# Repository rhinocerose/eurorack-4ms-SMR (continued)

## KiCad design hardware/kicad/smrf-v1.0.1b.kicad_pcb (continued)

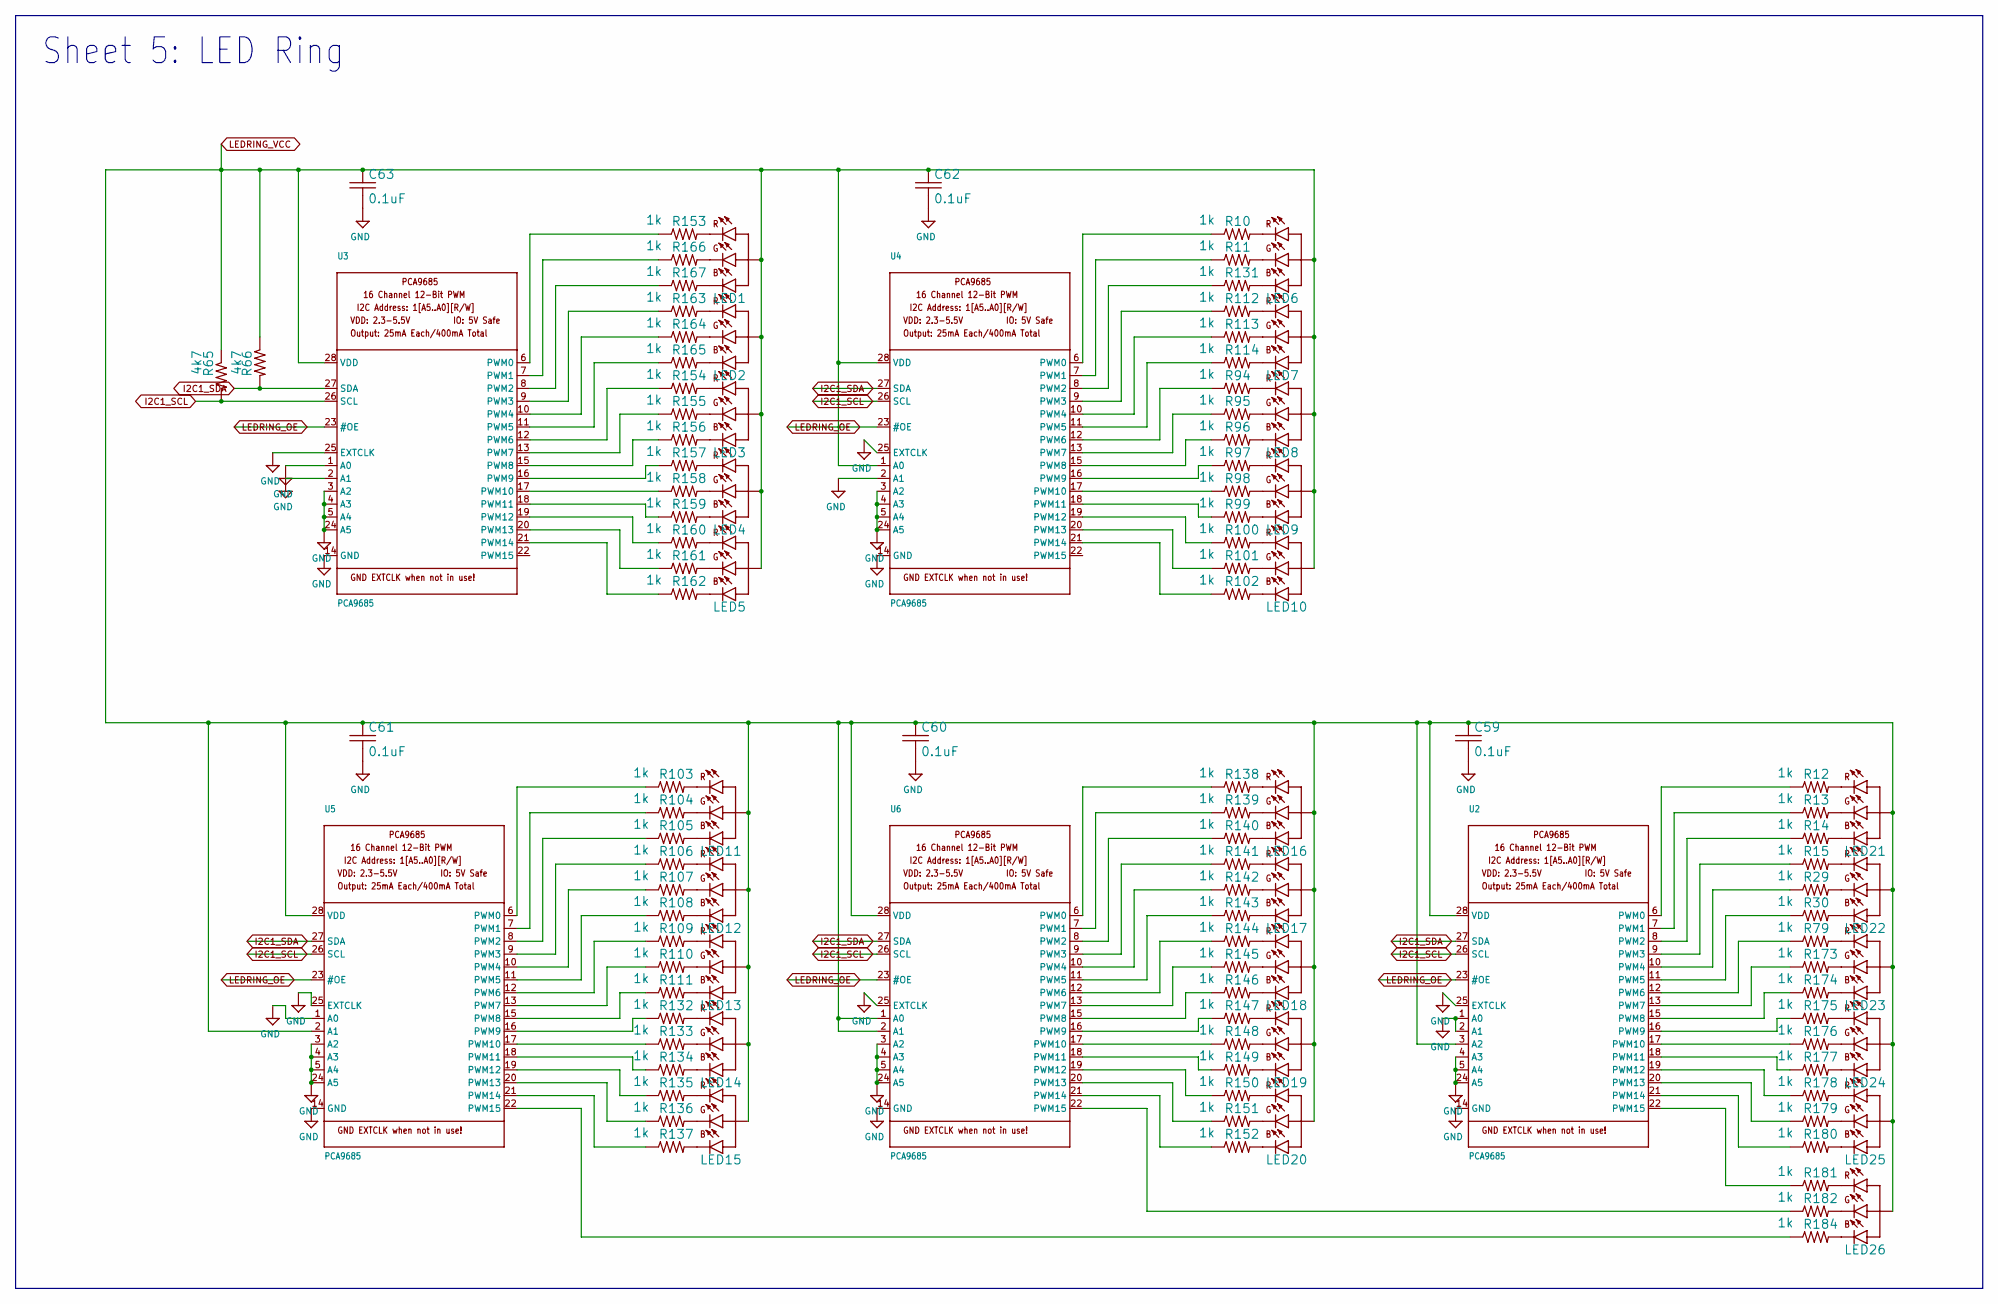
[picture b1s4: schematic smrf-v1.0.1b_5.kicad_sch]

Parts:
C59, C60, C61, C62, C63: 0.1uF; C0603
LED1, LED2, LED3, LED4, LED5, LED6, LED7, LED8, LED9, LED10, LED11, LED12, LED13, LED14, LED15, LED16, LED17, LED18, LED19, LED20, LED21, LED22, LED23, LED24, LED25, LED26: LED-RGB-CA-HEBEI; PLCC4
R10, R11, R12, R13, R14, R15, R29, R30, R79, R94, R95, R96, R97, R98, R99, R100, R101, R102, R103, R104, R105, R106, R107, R108, R109, R110, R111, R112, R113, R114, R131, R132, R133, R134, R135, R136, R137, R138, R139, R140, R141, R142, R143, R144, R145, R146, R147, R148, R149, R150, R151, R152, R153, R154, R155, R156, R157, R158, R159, R160, R161, R162, R163, R164, R165, R166, R167, R173, R174, R175, R176, R177, R178, R179, R180, R181, R182, R184: 1k; R0603
R65, R66: 4k7; R0603
U2, U3, U4, U5, U6: PCA9685; TSSOP28

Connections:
GND: C59.2, C60.2, C61.2, C62.2, C63.2, U2.1 (A0), U2.2 (A1), U2.4 (A3), U2.5 (A4), U2.14 (GND), U2.24 (A5), U2.25 (EXTCLK), U3.1 (A0), U3.2 (A1), U3.3 (A2), U3.4 (A3), U3.5 (A4), U3.14 (GND), U3.24 (A5), U3.25 (EXTCLK), U4.2 (A1), U4.3 (A2), U4.4 (A3), U4.5 (A4), U4.14 (GND), U4.24 (A5), U4.25 (EXTCLK), U5.1 (A0), U5.3 (A2), U5.4 (A3), U5.5 (A4), U5.14 (GND), U5.24 (A5), U5.25 (EXTCLK), U6.3 (A2), U6.4 (A3), U6.5 (A4), U6.14 (GND), U6.24 (A5), U6.25 (EXTCLK); also elsewhere on the board
I2C1_SCL: R65.2, U2.26 (SCL), U3.26 (SCL), U4.26 (SCL), U5.26 (SCL), U6.26 (SCL); also elsewhere on the board
I2C1_SDA: R66.2, U2.27 (SDA), U3.27 (SDA), U4.27 (SDA), U5.27 (SDA), U6.27 (SDA); also elsewhere on the board
LEDRING_OE: U2.23 (#OE), U3.23 (#OE), U4.23 (#OE), U5.23 (#OE), U6.23 (#OE); also elsewhere on the board
LEDRING_VCC: C59.1, C60.1, C61.1, C62.1, C63.1, LED1.P$2 (A), LED2.P$2 (A), LED3.P$2 (A), LED4.P$2 (A), LED5.P$2 (A), LED6.P$2 (A), LED7.P$2 (A), LED8.P$2 (A), LED9.P$2 (A), LED10.P$2 (A), LED11.P$2 (A), LED12.P$2 (A), LED13.P$2 (A), LED14.P$2 (A), LED15.P$2 (A), LED16.P$2 (A), LED17.P$2 (A), LED18.P$2 (A), LED19.P$2 (A), LED20.P$2 (A), LED21.P$2 (A), LED22.P$2 (A), LED23.P$2 (A), LED24.P$2 (A), LED25.P$2 (A), LED26.P$2 (A), R65.1, R66.1, U2.3 (A2), U2.28 (VDD), U3.28 (VDD), U4.1 (A0), U4.28 (VDD), U5.2 (A1), U5.28 (VDD), U6.1 (A0), U6.2 (A1), U6.28 (VDD); also elsewhere on the board
unnamed: LED1.P$1 (CR), R153.2
unnamed: LED1.P$4 (CG), R166.2
unnamed: R12.1, U2.6 (PWM0)
unnamed: R13.1, U2.7 (PWM1)
unnamed: R14.1, U2.8 (PWM2)
unnamed: R15.1, U2.9 (PWM3)
unnamed: LED1.P$3 (CB), R167.2
unnamed: R29.1, U2.10 (PWM4)
unnamed: R30.1, U2.11 (PWM5)
unnamed: LED2.P$1 (CR), R163.2
unnamed: LED2.P$4 (CG), R164.2
unnamed: LED2.P$3 (CB), R165.2
unnamed: LED3.P$1 (CR), R154.2
unnamed: LED3.P$4 (CG), R155.2
unnamed: LED3.P$3 (CB), R156.2
unnamed: LED4.P$1 (CR), R157.2
unnamed: LED4.P$4 (CG), R158.2
unnamed: LED4.P$3 (CB), R159.2
unnamed: R79.1, U2.12 (PWM6)
unnamed: R173.1, U2.13 (PWM7)
unnamed: R174.1, U2.15 (PWM8)
unnamed: LED5.P$1 (CR), R160.2
unnamed: LED5.P$4 (CG), R161.2
unnamed: LED5.P$3 (CB), R162.2
unnamed: LED6.P$1 (CR), R10.2
unnamed: LED6.P$4 (CG), R11.2
unnamed: LED6.P$3 (CB), R131.2
unnamed: LED7.P$1 (CR), R112.2
unnamed: LED7.P$4 (CG), R113.2
unnamed: LED7.P$3 (CB), R114.2
unnamed: LED8.P$1 (CR), R94.2
unnamed: LED8.P$4 (CG), R95.2
unnamed: LED8.P$3 (CB), R96.2
unnamed: LED9.P$1 (CR), R97.2
unnamed: LED9.P$4 (CG), R98.2
unnamed: LED9.P$3 (CB), R99.2
unnamed: LED10.P$1 (CR), R100.2
unnamed: LED10.P$4 (CG), R101.2
unnamed: LED10.P$3 (CB), R102.2
unnamed: LED11.P$1 (CR), R103.2
unnamed: R175.1, U2.16 (PWM9)
unnamed: LED11.P$4 (CG), R104.2
unnamed: LED11.P$3 (CB), R105.2
unnamed: LED12.P$1 (CR), R106.2
unnamed: LED12.P$4 (CG), R107.2
unnamed: LED12.P$3 (CB), R108.2
unnamed: LED13.P$1 (CR), R109.2
unnamed: LED13.P$4 (CG), R110.2
unnamed: LED14.P$1 (CR), R132.2
unnamed: LED14.P$4 (CG), R133.2
unnamed: LED14.P$3 (CB), R134.2
unnamed: LED15.P$1 (CR), R135.2
unnamed: LED15.P$4 (CG), R136.2
unnamed: R176.1, U2.17 (PWM10)
unnamed: R177.1, U2.18 (PWM11)
unnamed: LED15.P$3 (CB), R137.2
unnamed: LED16.P$1 (CR), R138.2
unnamed: LED16.P$4 (CG), R139.2
unnamed: LED16.P$3 (CB), R140.2
unnamed: LED17.P$1 (CR), R141.2
unnamed: LED17.P$4 (CG), R142.2
unnamed: LED17.P$3 (CB), R143.2
unnamed: LED18.P$1 (CR), R144.2
unnamed: LED18.P$4 (CG), R145.2
unnamed: LED18.P$3 (CB), R146.2
unnamed: LED19.P$1 (CR), R147.2
unnamed: LED19.P$4 (CG), R148.2
unnamed: LED19.P$3 (CB), R149.2
unnamed: LED20.P$1 (CR), R150.2
unnamed: LED20.P$4 (CG), R151.2
unnamed: LED20.P$3 (CB), R152.2
unnamed: LED13.P$3 (CB), R111.2
unnamed: R153.1, U3.6 (PWM0)
unnamed: R166.1, U3.7 (PWM1)
unnamed: R167.1, U3.8 (PWM2)
unnamed: R163.1, U3.9 (PWM3)
unnamed: R164.1, U3.10 (PWM4)
unnamed: R165.1, U3.11 (PWM5)
unnamed: R154.1, U3.12 (PWM6)
unnamed: R155.1, U3.13 (PWM7)
unnamed: R156.1, U3.15 (PWM8)
unnamed: R157.1, U3.16 (PWM9)
unnamed: R158.1, U3.17 (PWM10)
unnamed: R159.1, U3.18 (PWM11)
unnamed: R160.1, U3.19 (PWM12)
unnamed: R161.1, U3.20 (PWM13)
unnamed: R162.1, U3.21 (PWM14)
unnamed: R178.1, U2.19 (PWM12)
unnamed: R10.1, U4.6 (PWM0)
unnamed: R11.1, U4.7 (PWM1)
unnamed: R131.1, U4.8 (PWM2)
unnamed: R112.1, U4.9 (PWM3)
unnamed: R113.1, U4.10 (PWM4)
unnamed: R114.1, U4.11 (PWM5)
unnamed: R94.1, U4.12 (PWM6)
unnamed: R95.1, U4.13 (PWM7)
unnamed: R96.1, U4.15 (PWM8)
unnamed: R97.1, U4.16 (PWM9)
unnamed: R98.1, U4.17 (PWM10)
unnamed: R99.1, U4.18 (PWM11)
unnamed: R100.1, U4.19 (PWM12)
unnamed: R101.1, U4.20 (PWM13)
unnamed: R102.1, U4.21 (PWM14)
unnamed: R179.1, U2.20 (PWM13)
unnamed: R103.1, U5.6 (PWM0)
unnamed: R104.1, U5.7 (PWM1)
unnamed: R105.1, U5.8 (PWM2)
unnamed: R106.1, U5.9 (PWM3)
unnamed: R107.1, U5.10 (PWM4)
unnamed: R108.1, U5.11 (PWM5)
unnamed: R109.1, U5.12 (PWM6)
unnamed: R110.1, U5.13 (PWM7)
unnamed: R111.1, U5.15 (PWM8)
unnamed: R132.1, U5.16 (PWM9)
unnamed: R133.1, U5.17 (PWM10)
unnamed: R134.1, U5.18 (PWM11)
unnamed: R135.1, U5.19 (PWM12)
unnamed: R136.1, U5.20 (PWM13)
unnamed: R137.1, U5.21 (PWM14)
unnamed: R180.1, U2.21 (PWM14)
unnamed: LED21.P$1 (CR), R12.2
unnamed: LED21.P$4 (CG), R13.2
unnamed: LED21.P$3 (CB), R14.2
unnamed: LED22.P$1 (CR), R15.2
unnamed: LED22.P$4 (CG), R29.2
unnamed: LED22.P$3 (CB), R30.2
unnamed: LED23.P$1 (CR), R79.2
unnamed: LED23.P$4 (CG), R173.2
unnamed: LED23.P$3 (CB), R174.2
unnamed: LED24.P$1 (CR), R175.2
unnamed: LED24.P$4 (CG), R176.2
unnamed: LED24.P$3 (CB), R177.2
unnamed: R138.1, U6.6 (PWM0)
unnamed: R139.1, U6.7 (PWM1)
unnamed: R140.1, U6.8 (PWM2)
unnamed: R141.1, U6.9 (PWM3)
unnamed: R142.1, U6.10 (PWM4)
unnamed: R143.1, U6.11 (PWM5)
unnamed: R144.1, U6.12 (PWM6)
unnamed: R145.1, U6.13 (PWM7)
unnamed: R146.1, U6.15 (PWM8)
unnamed: R147.1, U6.16 (PWM9)
unnamed: R148.1, U6.17 (PWM10)
unnamed: R149.1, U6.18 (PWM11)
unnamed: R150.1, U6.19 (PWM12)
unnamed: R151.1, U6.20 (PWM13)
unnamed: R152.1, U6.21 (PWM14)
unnamed: LED25.P$1 (CR), R178.2
unnamed: LED25.P$4 (CG), R179.2
unnamed: LED25.P$3 (CB), R180.2
unnamed: LED26.P$1 (CR), R181.2
unnamed: LED26.P$4 (CG), R182.2
unnamed: LED26.P$3 (CB), R184.2
unnamed: R181.1, U2.22 (PWM15)
unnamed: R182.1, U6.22 (PWM15)
unnamed: R184.1, U5.22 (PWM15)

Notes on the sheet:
Sheet 5: LED Ring

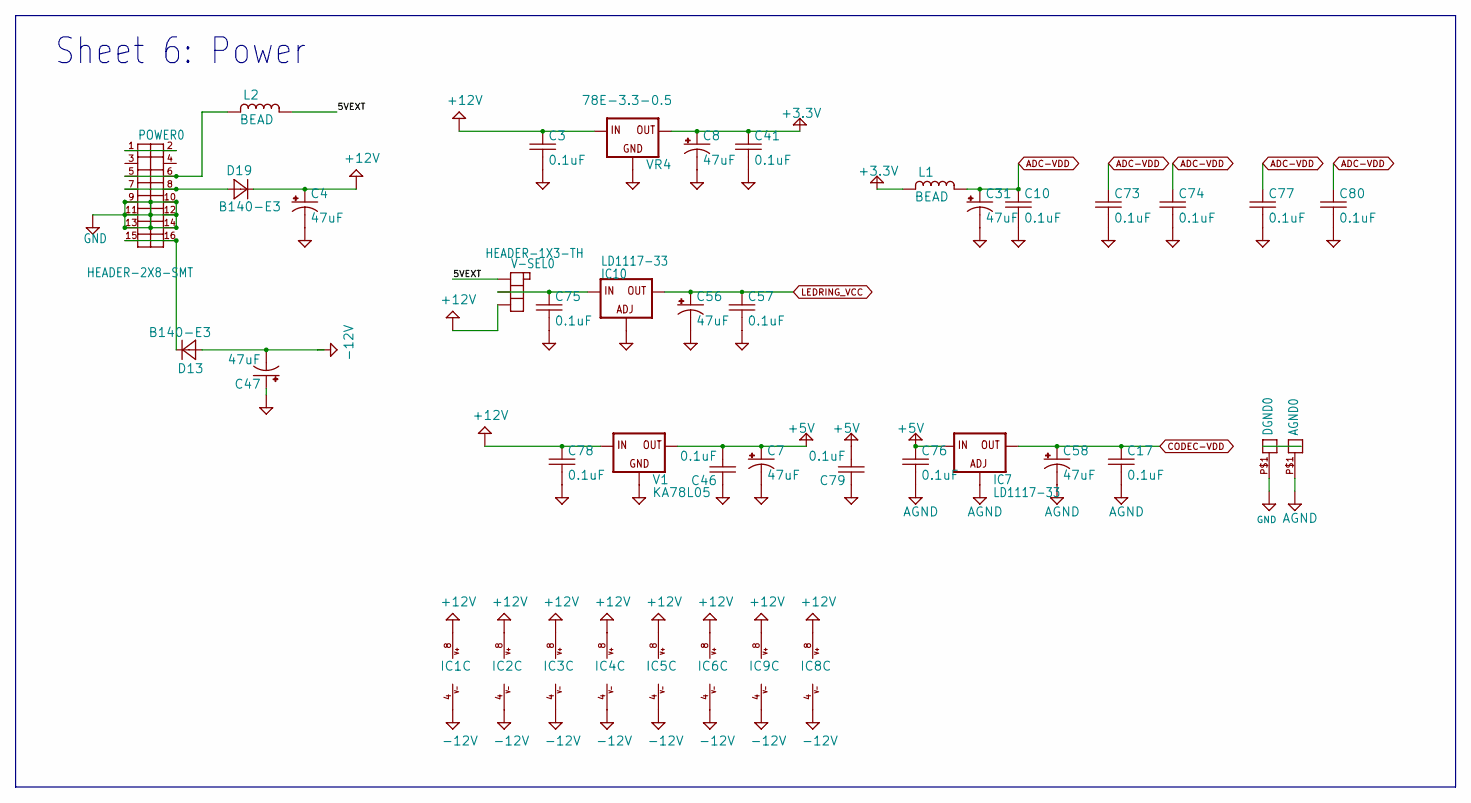
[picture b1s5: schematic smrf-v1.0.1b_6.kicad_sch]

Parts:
AGND0: PAD-06
C3, C10, C17, C41, C46, C57, C73, C74, C75, C76, C77, C78, C79, C80: 0.1uF; C0603
C4, C7, C8, C31, C47, C56, C58: 47uF; C-POL-5
D13, D19: B140-E3; SMA
DGND0: PAD-06
IC1, IC2, IC3, IC4, IC5, IC6, IC8, IC9: TL082; TSSOP8
IC7, IC10: LD1117-33; SOT223
L1, L2: BEAD; 0603
POWER0: HEADER-2X8-SMT; HEADER-2X8-SMT-SHROUDED
V1: KA78L05; SOT89
V-SEL0: HEADER-1X3-TH
VR4: 78E-3.3-0.5; RECOM-DCDC

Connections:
5VEXT: L2.2 (4), V-SEL0.P$1
+3.3V: C8.+, C41.1, L1.1, VR4.P$3 (OUT); also elsewhere on the board
+5V: C7.+, C46.2, C76.1, C79.2, IC7.3 (IN), V1.1 (OUT); also elsewhere on the board
+12V: C3.1, C4.+, C78.1, D19.K (C), IC1.8 (V+), IC2.8 (V+), IC3.8 (V+), IC4.8 (V+), IC5.8 (V+), IC6.8 (V+), IC8.8 (V+), IC9.8 (V+), V1.3 (IN), V-SEL0.P$3, VR4.P$1 (IN)
-12V: C47.-, D13.A, IC1.4 (V-), IC2.4 (V-), IC3.4 (V-), IC4.4 (V-), IC5.4 (V-), IC6.4 (V-), IC8.4 (V-), IC9.4 (V-)
ADC-VDD: C10.1, C31.+, C73.1, C74.1, C77.1, C80.1, L1.2 (4); also elsewhere on the board
AGND: AGND0.P$1, C17.2, C58.-, C76.2, IC7.1 (ADJ); also elsewhere on the board
CODEC-VDD: C17.1, C58.+, IC7.2 (OUT), IC7.4 (OUT); also elsewhere on the board
GND: C3.2, C4.-, C7.-, C8.-, C10.2, C31.-, C41.2, C46.1, C47.+, C56.-, C57.2, C73.2, C74.2, C75.2, C77.2, C78.2, C79.1, C80.2, DGND0.P$1, IC10.1 (ADJ), POWER0.9, POWER0.10, POWER0.11, POWER0.12, POWER0.13, POWER0.14, V1.2A (GND), V1.2B (GND), VR4.P$2 (GND); also elsewhere on the board
LEDRING_VCC: C56.+, C57.1, IC10.2 (OUT), IC10.4 (OUT); also elsewhere on the board
unnamed: C75.1, IC10.3 (IN), V-SEL0.P$2
unnamed: L2.1, POWER0.5, POWER0.6
unnamed: D19.A, POWER0.7, POWER0.8
unnamed: D13.K (C), POWER0.15, POWER0.16
unnamed: POWER0.1, POWER0.2

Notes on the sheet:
Sheet 6: Power

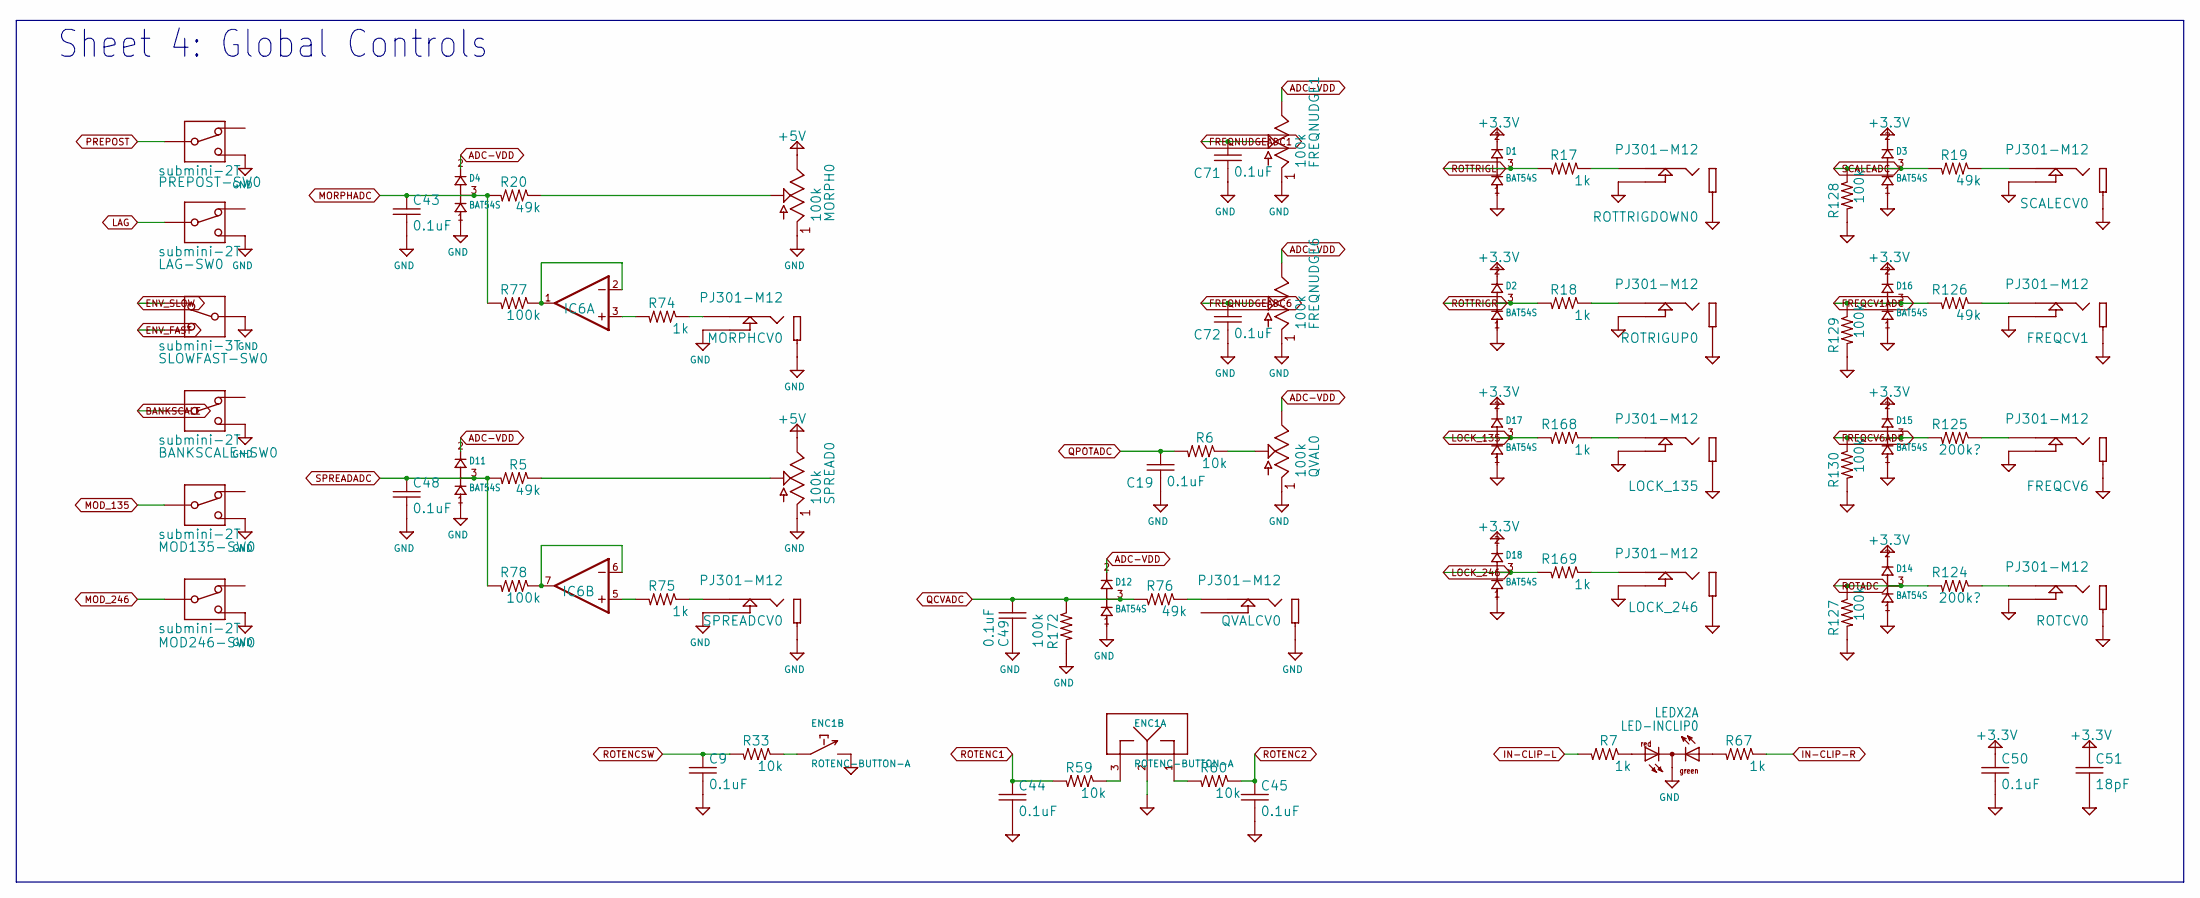
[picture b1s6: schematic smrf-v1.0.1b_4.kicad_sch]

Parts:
BANKSCALE-SW0: submini-2T; SPDT-SUB
C9, C19, C43, C44, C45, C48, C49, C50, C71, C72: 0.1uF; C0603
C51: 18pF; C0603
D1, D2, D3, D4, D11, D12, D14, D15, D16, D17, D18: BAT54S; SOT23
ENC1: ROTENC-BUTTON-A; ROTENC-12MM-BUT
FREQCV1, FREQCV6: PJ301-M12; PJ301M-12-FIX
FREQNUDGE1, FREQNUDGE6: 100k; POT-9MM-SONGHUEI
IC6: TL082; TSSOP8
LAG-SW0: submini-2T; SPDT-SUB
LED-INCLIP0: LEDX2A; LED-T1X2
LOCK_135, LOCK_246: PJ301-M12; PJ301M-12-FIX
MOD135-SW0, MOD246-SW0: submini-2T; SPDT-SUB
MORPH0: 100k; POT-9MM-SONGHUEI
MORPHCV0: PJ301-M12; PJ301M-12-FIX
PREPOST-SW0: submini-2T; SPDT-SUB
QVAL0: 100k; POT-9MM-SONGHUEI
QVALCV0: PJ301-M12; PJ301M-12-FIX
R5, R19, R20, R76, R126: 49k; R0603
R6, R33, R59, R60: 10k; R0603
R7, R17, R18, R67, R74, R75, R168, R169: 1k; R0603
R77, R78, R127, R128, R129, R130, R172: 100k; R0603
R124, R125: 200k?; R0603
ROTCV0: PJ301-M12; PJ301M-12-FIX
ROTRIGUP0: PJ301-M12; PJ301M-12-FIX
ROTTRIGDOWN0: PJ301-M12; PJ301M-12-FIX
SCALECV0: PJ301-M12; PJ301M-12-FIX
SLOWFAST-SW0: submini-3T; SPDT-SUB
SPREAD0: 100k; POT-9MM-SONGHUEI
SPREADCV0: PJ301-M12; PJ301M-12-FIX

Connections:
+3.3V: C50.1, C51.1, D1.2 (CATHODE), D2.2 (CATHODE), D3.2 (CATHODE), D14.2 (CATHODE), D15.2 (CATHODE), D16.2 (CATHODE), D17.2 (CATHODE), D18.2 (CATHODE); also elsewhere on the board
+5V: MORPH0.3, SPREAD0.3; also elsewhere on the board
ADC-VDD: D4.2 (CATHODE), D11.2 (CATHODE), D12.2 (CATHODE), FREQNUDGE1.3, FREQNUDGE6.3, QVAL0.3; also elsewhere on the board
BANKSCALE: BANKSCALE-SW0.P$2; also elsewhere on the board
ENV_FAST: SLOWFAST-SW0.P$1; also elsewhere on the board
ENV_SLOW: SLOWFAST-SW0.P$3; also elsewhere on the board
FREQCV1ADC: D16.3 (COMMON), R126.2, R129.1; also elsewhere on the board
FREQCV6ADC: D15.3 (COMMON), R125.2, R130.1; also elsewhere on the board
FREQNUDGEADC1: C71.1, FREQNUDGE1.2; also elsewhere on the board
FREQNUDGEADC6: C72.1, FREQNUDGE6.2; also elsewhere on the board
GND: BANKSCALE-SW0.P$1, C9.2, C19.2, C43.2, C44.2, C45.2, C48.2, C49.2, C50.2, C51.2, C71.2, C72.2, D1.1 (ANODE), D2.1 (ANODE), D3.1 (ANODE), D4.1 (ANODE), D11.1 (ANODE), D12.1 (ANODE), D14.1 (ANODE), D15.1 (ANODE), D16.1 (ANODE), D17.1 (ANODE), D18.1 (ANODE), ENC1.2, ENC1.SW2, FREQCV1.2 (SLEEVE), FREQCV1.3 (TIP-SW), FREQCV6.2 (SLEEVE), FREQCV6.3 (TIP-SW), FREQNUDGE1.1, FREQNUDGE6.1, LAG-SW0.P$1, LED-INCLIP0.K-2 (C), LOCK_135.2 (SLEEVE), LOCK_135.3 (TIP-SW), LOCK_246.2 (SLEEVE), LOCK_246.3 (TIP-SW), MOD135-SW0.P$1, MOD246-SW0.P$1, MORPH0.1, MORPHCV0.2 (SLEEVE), MORPHCV0.3 (TIP-SW), PREPOST-SW0.P$1, QVAL0.1, QVALCV0.2 (SLEEVE), R127.2, R128.2, R129.2, R130.2, R172.2, ROTCV0.2 (SLEEVE), ROTCV0.3 (TIP-SW), ROTRIGUP0.2 (SLEEVE), ROTRIGUP0.3 (TIP-SW), ROTTRIGDOWN0.2 (SLEEVE), ROTTRIGDOWN0.3 (TIP-SW), SCALECV0.2 (SLEEVE), SCALECV0.3 (TIP-SW), SLOWFAST-SW0.P$2, SPREAD0.1, SPREADCV0.2 (SLEEVE), SPREADCV0.3 (TIP-SW); also elsewhere on the board
IN-CLIP-L: R7.2; also elsewhere on the board
IN-CLIP-R: R67.1; also elsewhere on the board
LAG: LAG-SW0.P$2; also elsewhere on the board
LOCK_135: D17.3 (COMMON), R168.2; also elsewhere on the board
LOCK_246: D18.3 (COMMON), R169.2; also elsewhere on the board
MOD_135: MOD135-SW0.P$2; also elsewhere on the board
MOD_246: MOD246-SW0.P$2; also elsewhere on the board
MORPHADC: C43.1, D4.3 (COMMON), R20.2, R77.2; also elsewhere on the board
unnamed: IC6.3 (+IN), R74.2
unnamed: MORPH0.2, R20.1
unnamed: IC6.5 (+IN), R75.2
unnamed: QVAL0.2, R6.1
unnamed: R17.1, ROTTRIGDOWN0.1 (TIP)
unnamed: R18.1, ROTRIGUP0.1 (TIP)
unnamed: R19.1, SCALECV0.1 (TIP)
unnamed: R5.1, SPREAD0.2
unnamed: ENC1.3, R59.1
unnamed: LOCK_135.1 (TIP), R168.1
unnamed: ENC1.SW1, R33.1
unnamed: LOCK_246.1 (TIP), R169.1
unnamed: LED-INCLIP0.A-1 (AR), R7.1
unnamed: LED-INCLIP0.A-3 (AG), R67.2
unnamed: ENC1.1, R60.2
unnamed: MORPHCV0.1 (TIP), R74.1
unnamed: R75.1, SPREADCV0.1 (TIP)
unnamed: QVALCV0.1 (TIP), R76.1
unnamed: IC6.1 (OUT), IC6.2 (-IN), R77.1
unnamed: IC6.6 (-IN), IC6.7 (OUT), R78.1
unnamed: R124.1, ROTCV0.1 (TIP)
unnamed: FREQCV6.1 (TIP), R125.1
unnamed: FREQCV1.1 (TIP), R126.1
PREPOST: PREPOST-SW0.P$2; also elsewhere on the board
QCVADC: C49.1, D12.3 (COMMON), R76.2, R172.1; also elsewhere on the board
QPOTADC: C19.1, R6.2; also elsewhere on the board
ROTADC: D14.3 (COMMON), R124.2, R127.1; also elsewhere on the board
ROTENC1: C44.1, R59.2; also elsewhere on the board
ROTENC2: C45.1, R60.1; also elsewhere on the board
ROTENCSW: C9.1, R33.2; also elsewhere on the board
ROTTRIGL: D1.3 (COMMON), R17.2; also elsewhere on the board
ROTTRIGR: D2.3 (COMMON), R18.2; also elsewhere on the board
SCALEADC: D3.3 (COMMON), R19.2, R128.1; also elsewhere on the board
SPREADADC: C48.1, D11.3 (COMMON), R5.2, R78.2; also elsewhere on the board

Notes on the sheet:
Sheet 4: Global Controls

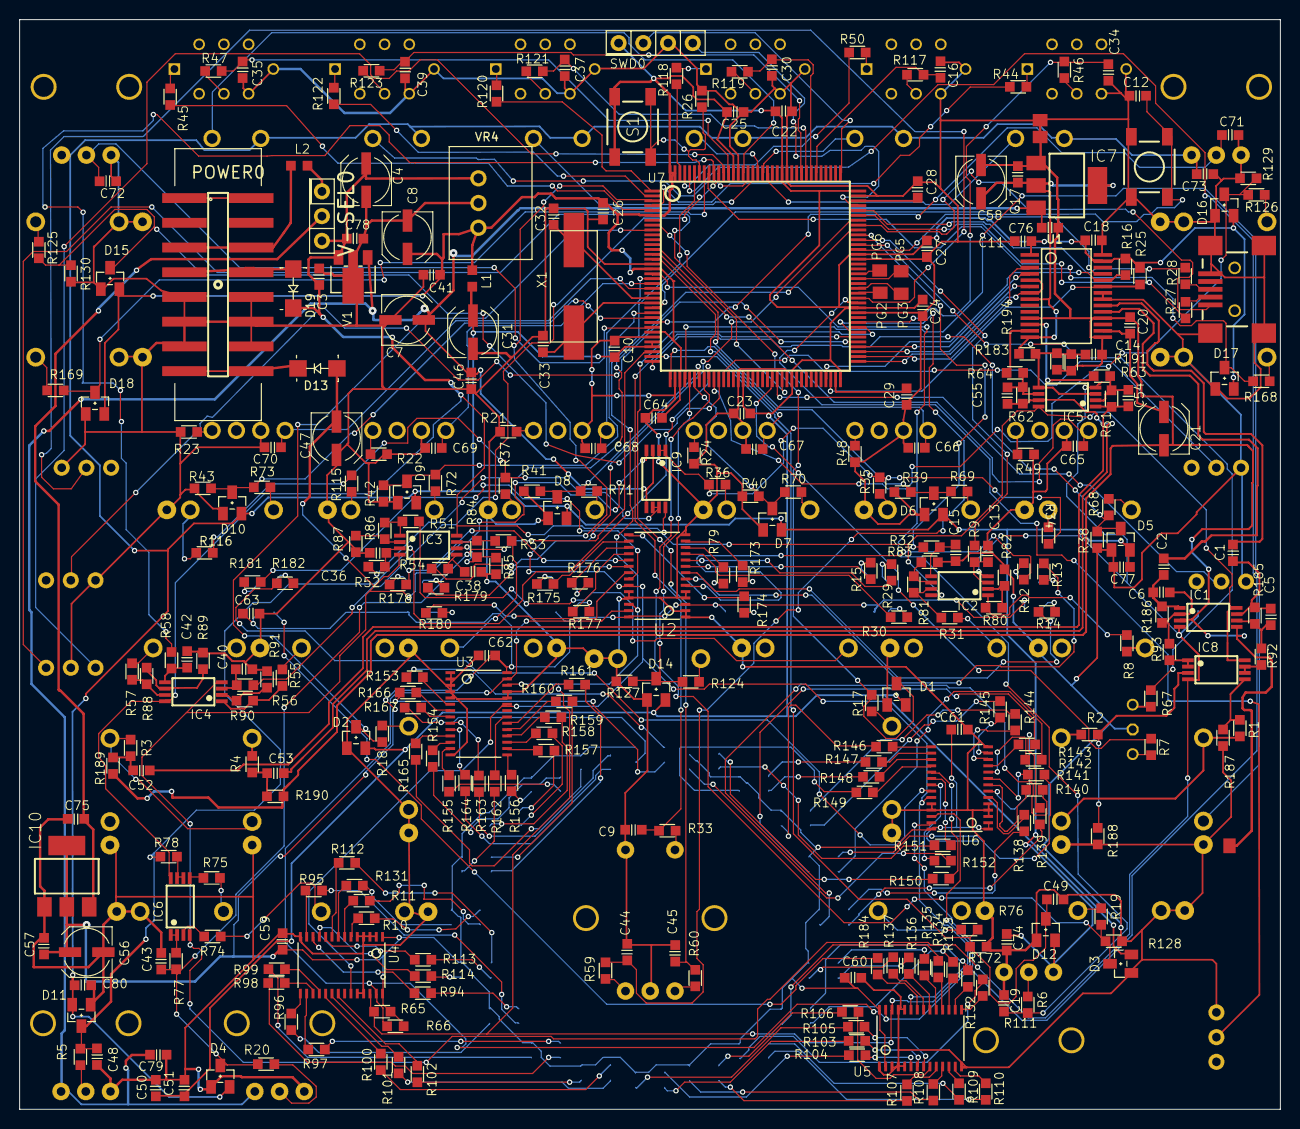
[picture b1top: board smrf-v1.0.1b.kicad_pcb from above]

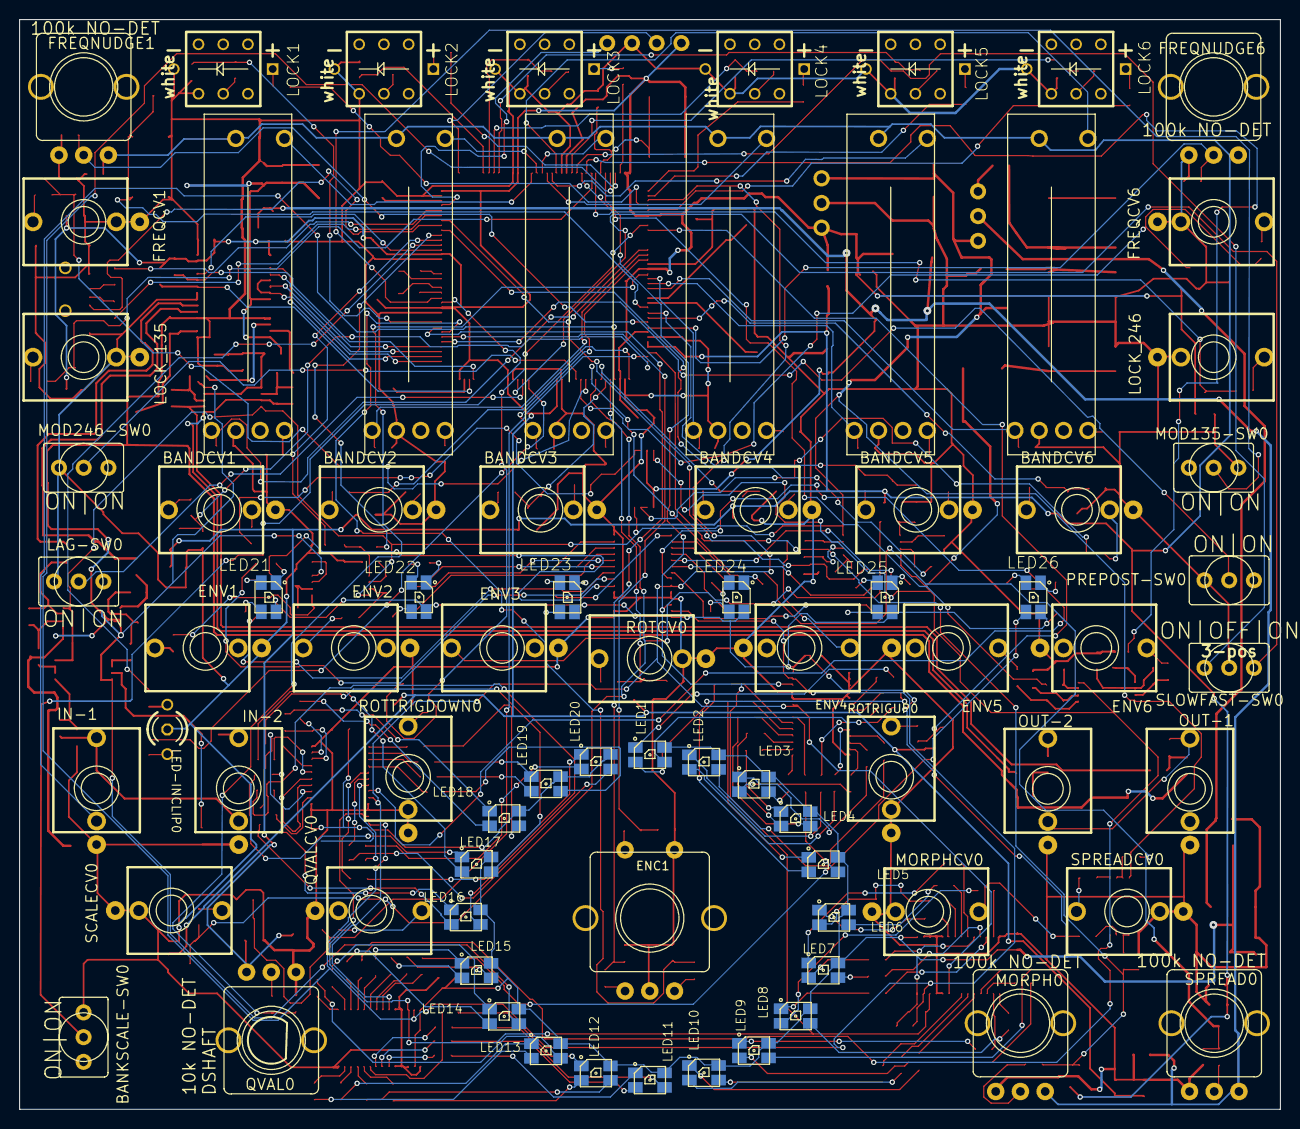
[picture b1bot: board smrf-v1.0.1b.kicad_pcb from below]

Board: 2 copper layers, 129.5 x 112.0 mm, 402 parts (78 on the bottom side), 364 nets.

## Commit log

2025-08-08 Kicad
2025-08-12 Update submodules to track main branch
2025-08-12 Update submodules: set branch=main and fix URLs
2025-08-12 Update submodules: add branch=main and fix URLs
2025-08-13 Remove .gitmodules (no submodules exist)
